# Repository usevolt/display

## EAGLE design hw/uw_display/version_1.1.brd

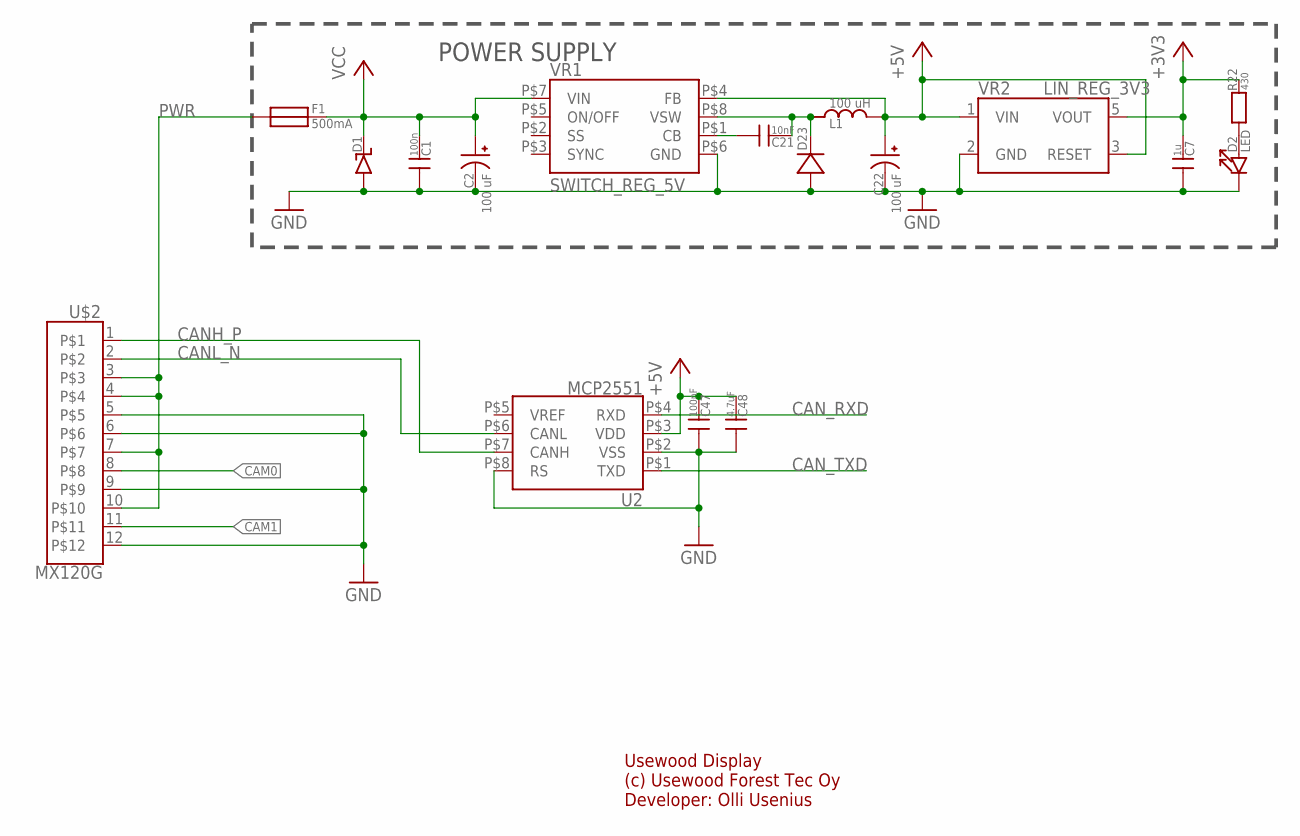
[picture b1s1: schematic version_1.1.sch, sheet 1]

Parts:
C1: 100n; 0603_SILKSCREEN
C2, C22: 100 uF; CAP_POL_SMD_10X10X10MM
C7: 1u; 0603_SILKSCREEN
C21: 10nF; 0603_SILKSCREEN
C47: 100nF; 0603_SILKSCREEN
C48: 4.7uF; 0603_SILKSCREEN
D1: DIODE_TVSDO-214AA; DO-214AB
D2: LED; 0603_SILKSCREEN
D23: DIODEDO219AB; DO219AB
F1: 500mA; MULTICOMP_MC36211
L1: 100 uH; INDUCTOR_BOURNS_10X13X5MM
R22: 430; 0603_SILKSCREEN
U2: MCP2551; SOIC8
U$2: MX120G; MOLEX_MX120G
VR1: SWITCH_REG_5V; SOIC8
VR2: LIN_REG_3V3; SOP5

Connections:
+3V3: C7.1, R22.1, VR2.5 (VOUT); also elsewhere on the board
+5V: C22.+, C47.1, C48.1, L1.P$2, U2.P$3 (VDD), VR1.P$4 (FB), VR2.1 (VIN), VR2.3 (RESET); also elsewhere on the board
CAM0: U$2.8; also elsewhere on the board
CAM1: U$2.11; also elsewhere on the board
CANH_P: U2.P$7 (CANH), U$2.1
CANL_N: U2.P$6 (CANL), U$2.2
CAN_RXD: U2.P$4 (RXD); also elsewhere on the board
CAN_TXD: U2.P$1 (TXD); also elsewhere on the board
GND: C1.0, C2.-, C7.0, C22.-, C47.0, C48.0, D1.P$1, D2.1, D23.P$1, U2.P$2 (VSS), U2.P$8 (RS), U$2.5, U$2.6, U$2.9, U$2.12, VR1.P$6 (GND), VR2.2 (GND); also elsewhere on the board
unnamed: D2.0, R22.0
unnamed: C21.1, D23.P$2 (N), L1.P$1, VR1.P$8 (VSW)
unnamed: C21.0, VR1.P$1 (CB)
PWR: F1.P$1, U$2.3, U$2.4, U$2.7, U$2.10
VCC: C1.1, C2.+, D1.P$2 (N), F1.P$2, VR1.P$7 (VIN); also elsewhere on the board

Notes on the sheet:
POWER SUPPLY
Usewood Display (c) Usewood Forest Tec Oy Developer: Olli Usenius

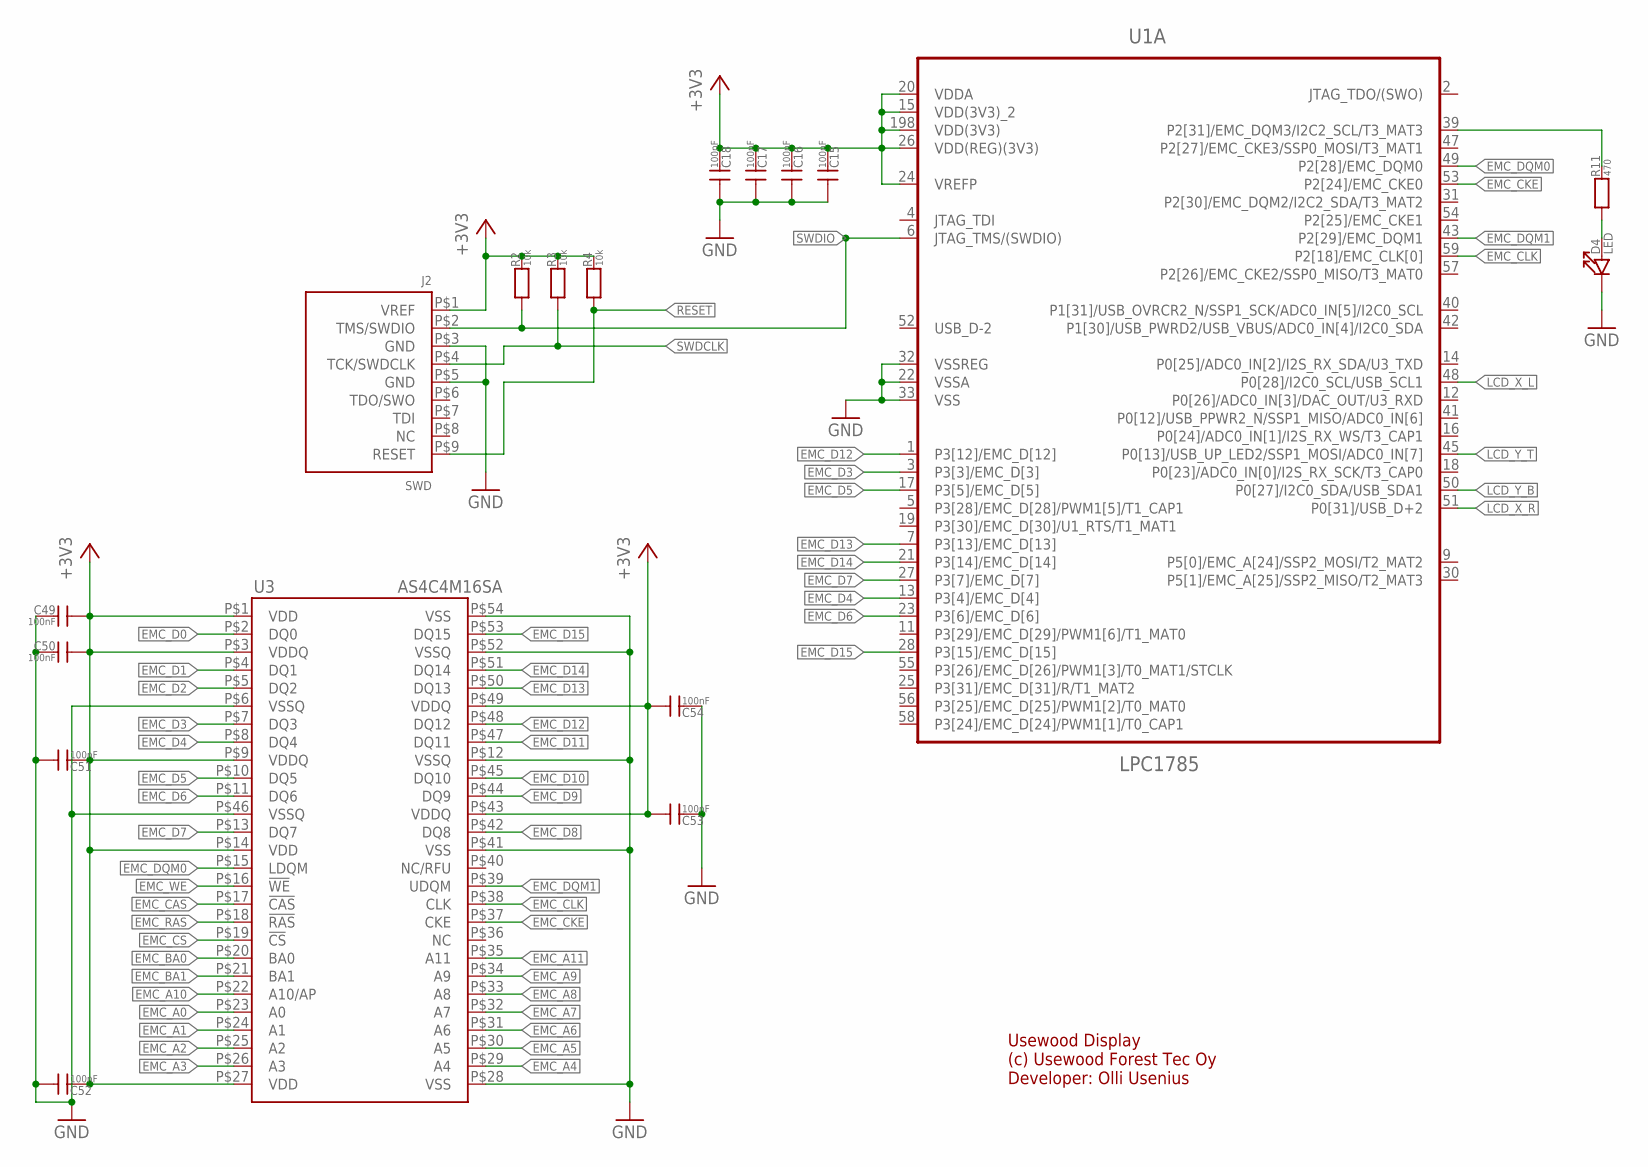
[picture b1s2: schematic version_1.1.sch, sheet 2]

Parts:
C15, C16, C17, C18, C49, C50, C51, C52, C53, C54: 100nF; 0603_SILKSCREEN
D4: LED; 0603_SILKSCREEN
J2: SWD; ARM_10_PIN_JTAG/SWD_CONNECTOR
R2, R3, R4: 10k; 0603_SILKSCREEN
R11: 470; 0603_SILKSCREEN
U1: LPC1785; QFP50P3000X3000X160-208N
U3: AS4C4M16SA; TSOP_II_54_PIN

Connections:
+3V3: C15.1, C16.1, C17.1, C18.1, C49.0, C50.0, C51.1, C52.1, C53.0, C54.0, J2.P$1 (VREF), R2.1, R3.1, R4.1, U1.15 (VDD(3V3)_2), U1.20 (VDDA), U1.24 (VREFP), U1.26 (VDD(REG)(3V3)), U1.198 (VDD(3V3)), U3.P$1 (VDD), U3.P$3 (VDDQ), U3.P$9 (VDDQ), U3.P$14 (VDD), U3.P$27 (VDD), U3.P$43 (VDDQ), U3.P$49 (VDDQ); also elsewhere on the board
EMC_A0: U3.P$23 (A0); also elsewhere on the board
EMC_A1: U3.P$24 (A1); also elsewhere on the board
EMC_A2: U3.P$25 (A2); also elsewhere on the board
EMC_A3: U3.P$26 (A3); also elsewhere on the board
EMC_A4: U3.P$29 (A4); also elsewhere on the board
EMC_A5: U3.P$30 (A5); also elsewhere on the board
EMC_A6: U3.P$31 (A6); also elsewhere on the board
EMC_A7: U3.P$32 (A7); also elsewhere on the board
EMC_A8: U3.P$33 (A8); also elsewhere on the board
EMC_A9: U3.P$34 (A9); also elsewhere on the board
EMC_A10: U3.P$22 (A10/AP); also elsewhere on the board
EMC_A11: U3.P$35 (A11); also elsewhere on the board
EMC_BA0: U3.P$20 (BA0); also elsewhere on the board
EMC_BA1: U3.P$21 (BA1); also elsewhere on the board
EMC_CAS: U3.P$17 (!CAS); also elsewhere on the board
EMC_CKE: U1.53 (P2[24]/EMC_CKE0), U3.P$37 (CKE)
EMC_CLK: U1.59 (P2[18]/EMC_CLK[0]), U3.P$38 (CLK)
EMC_CS: U3.P$19 (!CS); also elsewhere on the board
EMC_D0: U3.P$2 (DQ0); also elsewhere on the board
EMC_D1: U3.P$4 (DQ1); also elsewhere on the board
EMC_D2: U3.P$5 (DQ2); also elsewhere on the board
EMC_D3: U1.3 (P3[3]/EMC_D[3]), U3.P$7 (DQ3)
EMC_D4: U1.13 (P3[4]/EMC_D[4]), U3.P$8 (DQ4)
EMC_D5: U1.17 (P3[5]/EMC_D[5]), U3.P$10 (DQ5)
EMC_D6: U1.23 (P3[6]/EMC_D[6]), U3.P$11 (DQ6)
EMC_D7: U1.27 (P3[7]/EMC_D[7]), U3.P$13 (DQ7)
EMC_D8: U3.P$42 (DQ8); also elsewhere on the board
EMC_D9: U3.P$44 (DQ9); also elsewhere on the board
EMC_D10: U3.P$45 (DQ10); also elsewhere on the board
EMC_D11: U3.P$47 (DQ11); also elsewhere on the board
EMC_D12: U1.1 (P3[12]/EMC_D[12]), U3.P$48 (DQ12)
EMC_D13: U1.7 (P3[13]/EMC_D[13]), U3.P$50 (DQ13)
EMC_D14: U1.21 (P3[14]/EMC_D[14]), U3.P$51 (DQ14)
EMC_D15: U1.28 (P3[15]/EMC_D[15]), U3.P$53 (DQ15)
EMC_DQM0: U1.49 (P2[28]/EMC_DQM0), U3.P$15 (LDQM)
EMC_DQM1: U1.43 (P2[29]/EMC_DQM1), U3.P$39 (UDQM)
EMC_RAS: U3.P$18 (!RAS); also elsewhere on the board
EMC_WE: U3.P$16 (!WE); also elsewhere on the board
GND: C15.0, C16.0, C17.0, C18.0, C49.1, C50.1, C51.0, C52.0, C53.1, C54.1, D4.1, J2.P$3 (GND), J2.P$5 (GND), U1.22 (VSSA), U1.32 (VSSREG), U1.33 (VSS), U3.P$6 (VSSQ), U3.P$12 (VSSQ), U3.P$28 (VSS), U3.P$41 (VSS), U3.P$46 (VSSQ), U3.P$52 (VSSQ), U3.P$54 (VSS); also elsewhere on the board
LCD_X_L: U1.48 (P0[28]/I2C0_SCL/USB_SCL1); also elsewhere on the board
LCD_X_R: U1.51 (P0[31]/USB_D+2); also elsewhere on the board
LCD_Y_B: U1.50 (P0[27]/I2C0_SDA/USB_SDA1); also elsewhere on the board
LCD_Y_T: U1.45 (P0[13]/USB_UP_LED2/SSP1_MOSI/ADC0_IN[7]); also elsewhere on the board
unnamed: D4.0, R11.0
unnamed: R11.1, U1.39 (P2[31]/EMC_DQM3/I2C2_SCL/T3_MAT3)
RESET: J2.P$9 (RESET), R4.0; also elsewhere on the board
SWDCLK: J2.P$4 (TCK/SWDCLK), R3.0; also elsewhere on the board
SWDIO: J2.P$2 (TMS/SWDIO), R2.0, U1.6 (JTAG_TMS/(SWDIO))

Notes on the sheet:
Usewood Display (c) Usewood Forest Tec Oy Developer: Olli Usenius

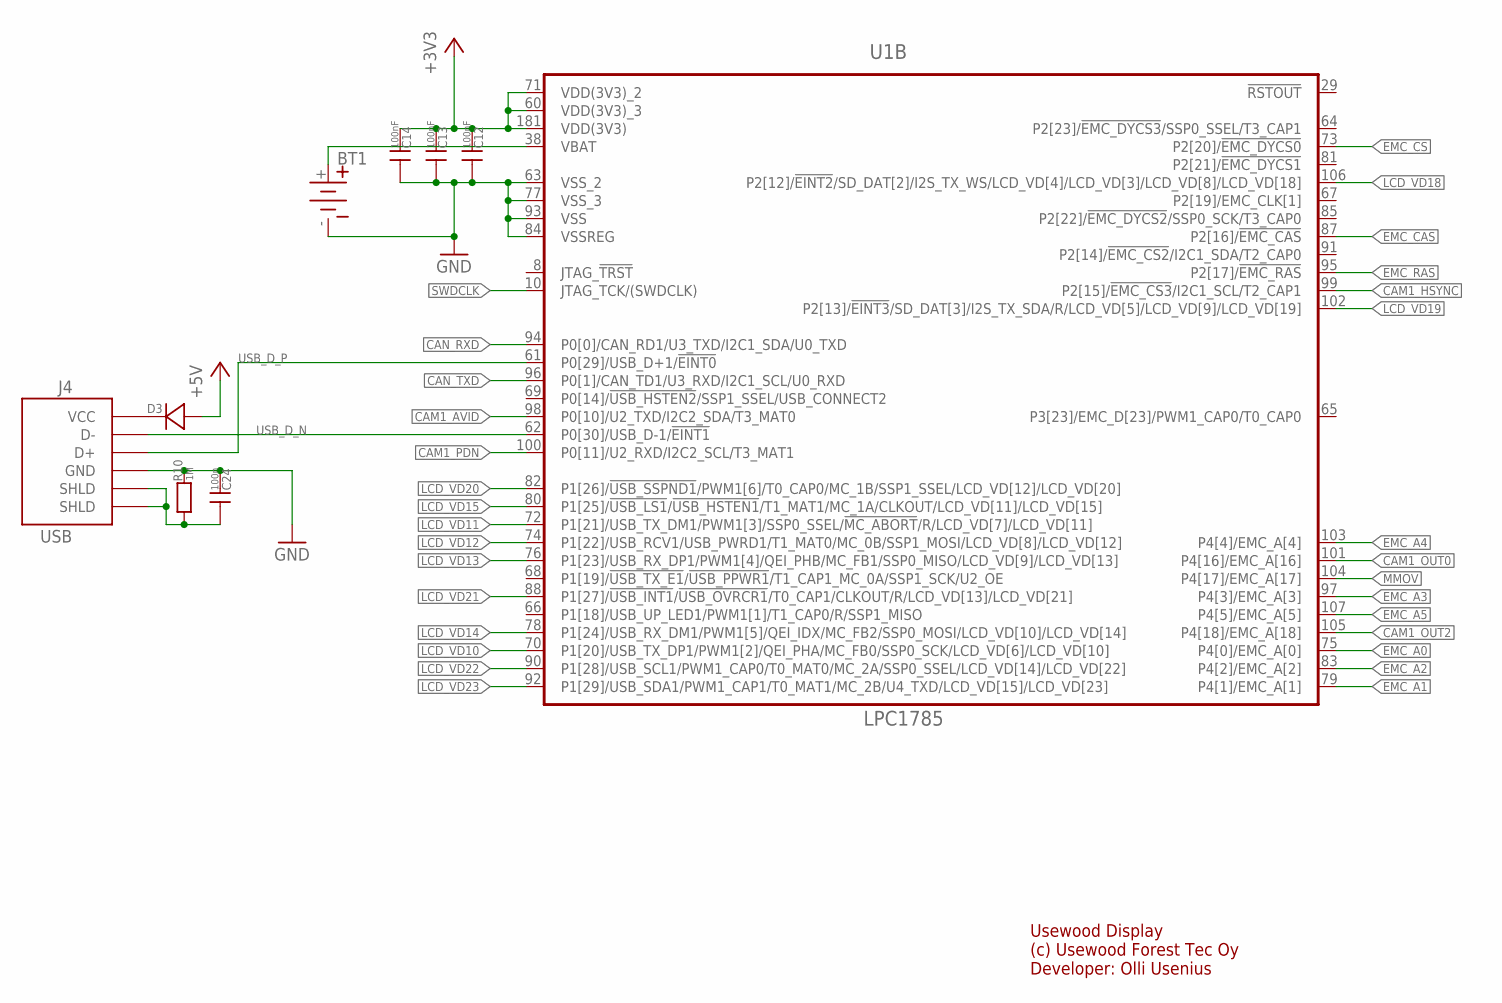
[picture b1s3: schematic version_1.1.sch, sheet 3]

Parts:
BT1: BAT; BATTERY_HOLDER_COIN_20MM_SMD
C12, C13, C14: 100nF; 0603_SILKSCREEN
C24: 100n; 0603_SILKSCREEN
D3: DIODEDO219AB; DO219AB
J4: USB; USB_A_RECEPTACLE_VERTICAL_MULTICOMP
R10: 1M; 0603_SILKSCREEN
U1: LPC1785; QFP50P3000X3000X160-208N

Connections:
+3V3: C12.1, C13.1, C14.1, U1.60 (VDD(3V3)_3), U1.71 (VDD(3V3)_2), U1.181 (VDD(3V3)); also elsewhere on the board
+5V: D3.P$1; also elsewhere on the board
CAM1_AVID: U1.98 (P0[10]/U2_TXD/I2C2_SDA/T3_MAT0); also elsewhere on the board
CAM1_HSYNC: U1.99 (P2[15]/!EMC_CS3!/I2C1_SCL/T2_CAP1); also elsewhere on the board
CAM1_OUT0: U1.101 (P4[16]/EMC_A[16]); also elsewhere on the board
CAM1_OUT2: U1.105 (P4[18]/EMC_A[18]); also elsewhere on the board
CAM1_PDN: U1.100 (P0[11]/U2_RXD/I2C2_SCL/T3_MAT1); also elsewhere on the board
CAN_RXD: U1.94 (P0[0]/CAN_RD1/U3_TXD/I2C1_SDA/U0_TXD); also elsewhere on the board
CAN_TXD: U1.96 (P0[1]/CAN_TD1/U3_RXD/I2C1_SCL/U0_RXD); also elsewhere on the board
EMC_A0: U1.75 (P4[0]/EMC_A[0]); also elsewhere on the board
EMC_A1: U1.79 (P4[1]/EMC_A[1]); also elsewhere on the board
EMC_A2: U1.83 (P4[2]/EMC_A[2]); also elsewhere on the board
EMC_A3: U1.97 (P4[3]/EMC_A[3]); also elsewhere on the board
EMC_A4: U1.103 (P4[4]/EMC_A[4]); also elsewhere on the board
EMC_A5: U1.107 (P4[5]/EMC_A[5]); also elsewhere on the board
EMC_CAS: U1.87 (P2[16]/!EMC_CAS!); also elsewhere on the board
EMC_CS: U1.73 (P2[20]/!EMC_DYCS0); also elsewhere on the board
EMC_RAS: U1.95 (P2[17]/!EMC_RAS); also elsewhere on the board
GND: BT1.-, C12.0, C13.0, C14.0, C24.1, J4.P$4 (GND), R10.1, U1.63 (VSS_2), U1.77 (VSS_3), U1.84 (VSSREG), U1.93 (VSS); also elsewhere on the board
LCD_VD10: U1.70 (P1[20]/USB_TX_DP1/PWM1[2]/QEI_PHA/MC_FB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); also elsewhere on the board
LCD_VD11: U1.72 (P1[21]/USB_TX_DM1/PWM1[3]/SSP0_SSEL/!MC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); also elsewhere on the board
LCD_VD12: U1.74 (P1[22]/USB_RCV1/USB_PWRD1/T1_MAT0/MC_0B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); also elsewhere on the board
LCD_VD13: U1.76 (P1[23]/USB_RX_DP1/PWM1[4]/QEI_PHB/MC_FB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); also elsewhere on the board
LCD_VD14: U1.78 (P1[24]/USB_RX_DM1/PWM1[5]/QEI_IDX/MC_FB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); also elsewhere on the board
LCD_VD15: U1.80 (P1[25]/!USB_LS1!/!USB_HSTEN1!/T1_MAT1/M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); also elsewhere on the board
LCD_VD18: U1.106 (P2[12]/!EINT2!/SD_DAT[2]/I2S_TX_WS/LCD_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); also elsewhere on the board
LCD_VD19: U1.102 (P2[13]/!EINT3!/SD_DAT[3]/I2S_TX_SDA/R/L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); also elsewhere on the board
LCD_VD20: U1.82 (P1[26]/!USB_SSPND1!/PWM1[6]/T0_CAP0/MC_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); also elsewhere on the board
LCD_VD21: U1.88 (P1[27]/!USB_INT1!/!USB_OVRCR1!/T0_CAP1/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); also elsewhere on the board
LCD_VD22: U1.90 (P1[28]/USB_SCL1/PWM1_CAP0/T0_MAT0/MC_2A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); also elsewhere on the board
LCD_VD23: U1.92 (P1[29]/USB_SDA1/PWM1_CAP1/T0_MAT1/MC_2B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); also elsewhere on the board
MMOV: U1.104 (P4[17]/EMC_A[17]); also elsewhere on the board
unnamed: BT1.+, U1.38 (VBAT)
unnamed: D3.P$2 (N), J4.P$1 (VCC)
unnamed: C24.0, J4.P$5 (SHLD), J4.P$6 (SHLD), R10.0
SWDCLK: U1.10 (JTAG_TCK/(SWDCLK)); also elsewhere on the board
USB_D_N: J4.P$2 (D-), U1.62 (P0[30]/USB_D-1/!EINT1)
USB_D_P: J4.P$3 (D+), U1.61 (P0[29]/USB_D+1/!EINT0)

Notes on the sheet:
Usewood Display (c) Usewood Forest Tec Oy Developer: Olli Usenius

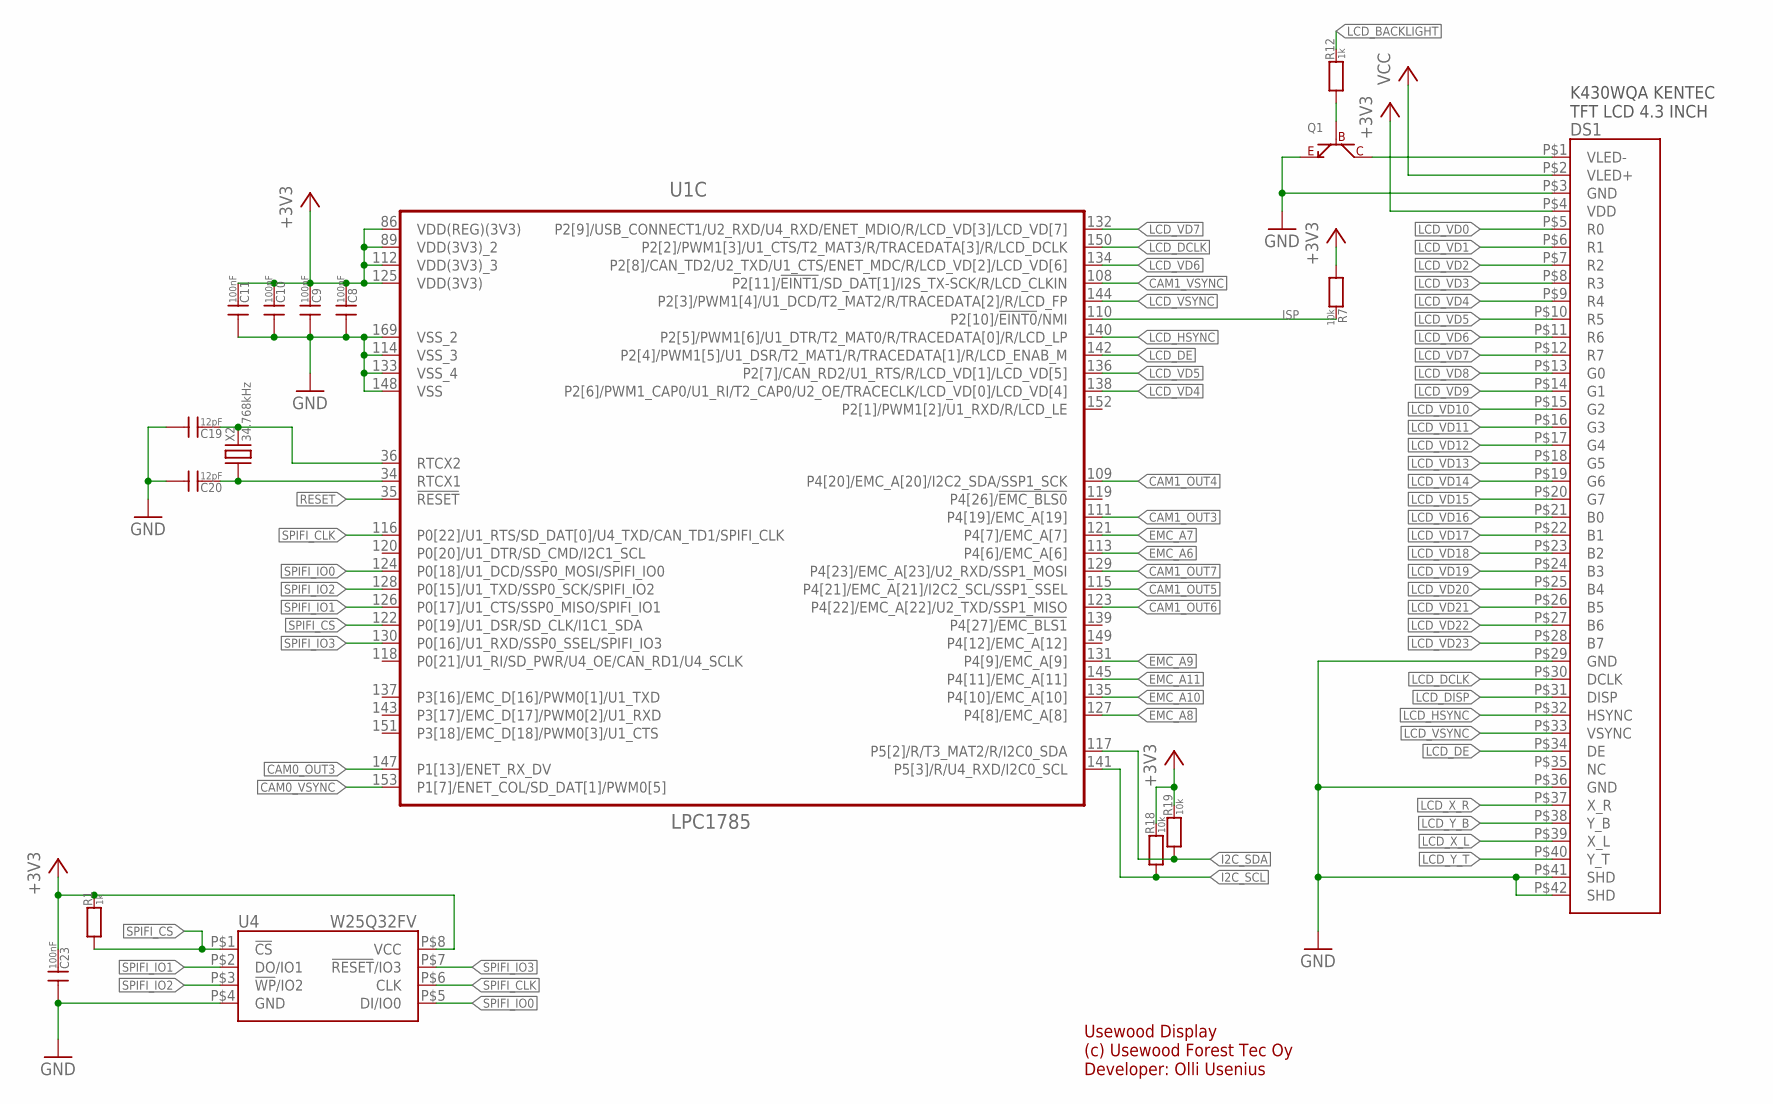
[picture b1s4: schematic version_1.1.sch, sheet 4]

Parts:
C8, C9, C10, C11, C23: 100nF; 0603_SILKSCREEN
C19, C20: 12pF; 0603_SILKSCREEN
DS1: KENTEC_TFT_LCD_4.3_INCHSMD; HEADER_KENTEC_TFT_LCD_4.3_INCH
Q1: NPN_TRANSISTORSOT323; SOT323
R1, R12: 1k; 0603_SILKSCREEN
R7, R18, R19: 10k; 0603_SILKSCREEN
U1: LPC1785; QFP50P3000X3000X160-208N
U4: W25Q32FV; SOIC8_W
X2: 34.768kHz; XTAL_ABS25

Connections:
+3V3: C8.1, C9.1, C10.1, C11.1, C23.1, DS1.P$4 (VDD), R1.1, R7.0, R18.1, R19.1, U1.86 (VDD(REG)(3V3)), U1.89 (VDD(3V3)_2), U1.112 (VDD(3V3)_3), U1.125 (VDD(3V3)), U4.P$8 (VCC); also elsewhere on the board
CAM0_OUT3: U1.147 (P1[13]/ENET_RX_DV); also elsewhere on the board
CAM0_VSYNC: U1.153 (P1[7]/ENET_COL/SD_DAT[1]/PWM0[5]); also elsewhere on the board
CAM1_OUT3: U1.111 (P4[19]/EMC_A[19]); also elsewhere on the board
CAM1_OUT4: U1.109 (P4[20]/EMC_A[20]/I2C2_SDA/SSP1_SCK); also elsewhere on the board
CAM1_OUT5: U1.115 (P4[21]/EMC_A[21]/I2C2_SCL/SSP1_SSEL); also elsewhere on the board
CAM1_OUT6: U1.123 (P4[22]/EMC_A[22]/U2_TXD/SSP1_MISO); also elsewhere on the board
CAM1_OUT7: U1.129 (P4[23]/EMC_A[23]/U2_RXD/SSP1_MOSI); also elsewhere on the board
CAM1_VSYNC: U1.108 (P2[11]/!EINT1!/SD_DAT[1]/I2S_TX-SCK/R/L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); also elsewhere on the board
EMC_A6: U1.113 (P4[6]/EMC_A[6]); also elsewhere on the board
EMC_A7: U1.121 (P4[7]/EMC_A[7]); also elsewhere on the board
EMC_A8: U1.127 (P4[8]/EMC_A[8]); also elsewhere on the board
EMC_A9: U1.131 (P4[9]/EMC_A[9]); also elsewhere on the board
EMC_A10: U1.135 (P4[10]/EMC_A[10]); also elsewhere on the board
EMC_A11: U1.145 (P4[11]/EMC_A[11]); also elsewhere on the board
GND: C8.0, C9.0, C10.0, C11.0, C19.0, C20.0, C23.0, DS1.P$3 (GND), DS1.P$29 (GND), DS1.P$36 (GND), DS1.P$41 (SHD), DS1.P$42 (SHD), Q1.R (E), U1.114 (VSS_3), U1.133 (VSS_4), U1.148 (VSS), U1.169 (VSS_2), U4.P$4 (GND); also elsewhere on the board
I2C_SCL: R18.0, U1.141 (P5[3]/R/U4_RXD/I2C0_SCL); also elsewhere on the board
I2C_SDA: R19.0, U1.117 (P5[2]/R/T3_MAT2/R/I2C0_SDA); also elsewhere on the board
ISP: R7.1, U1.110 (P2[10]/!EINT0!/NMI)
LCD_BACKLIGHT: R12.1; also elsewhere on the board
LCD_DCLK: DS1.P$30 (DCLK), U1.150 (P2[2]/PWM1[3]/U1_CTS/T2_MAT3/R/TRACEDAT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)
LCD_DE: DS1.P$34 (DE), U1.142 (P2[4]/PWM1[5]/U1_DSR/T2_MAT1/R/TRACEDAT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)
LCD_DISP: DS1.P$31 (DISP); also elsewhere on the board
LCD_HSYNC: DS1.P$32 (HSYNC), U1.140 (P2[5]/PWM1[6]/U1_DTR/T2_MAT0/R/TRACEDAT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)
LCD_VD0: DS1.P$5 (R0); also elsewhere on the board
LCD_VD1: DS1.P$6 (R1); also elsewhere on the board
LCD_VD2: DS1.P$7 (R2); also elsewhere on the board
LCD_VD3: DS1.P$8 (R3); also elsewhere on the board
LCD_VD4: DS1.P$9 (R4), U1.138 (P2[6]/PWM1_CAP0/U1_RI/T2_CAP0/U2_OE/TRA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)
LCD_VD5: DS1.P$10 (R5), U1.136 (P2[7]/CAN_RD2/U1_RTS/R/LCD_VD[1]/LCD_VD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)
LCD_VD6: DS1.P$11 (R6), U1.134 (P2[8]/CAN_TD2/U2_TXD/U1_CTS/ENET_MDC/R/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)
LCD_VD7: DS1.P$12 (R7), U1.132 (P2[9]/USB_CONNECT1/U2_RXD/U4_RXD/ENET_M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)
LCD_VD8: DS1.P$13 (G0); also elsewhere on the board
LCD_VD9: DS1.P$14 (G1); also elsewhere on the board
LCD_VD10: DS1.P$15 (G2); also elsewhere on the board
LCD_VD11: DS1.P$16 (G3); also elsewhere on the board
LCD_VD12: DS1.P$17 (G4); also elsewhere on the board
LCD_VD13: DS1.P$18 (G5); also elsewhere on the board
LCD_VD14: DS1.P$19 (G6); also elsewhere on the board
LCD_VD15: DS1.P$20 (G7); also elsewhere on the board
LCD_VD16: DS1.P$21 (B0); also elsewhere on the board
LCD_VD17: DS1.P$22 (B1); also elsewhere on the board
LCD_VD18: DS1.P$23 (B2); also elsewhere on the board
LCD_VD19: DS1.P$24 (B3); also elsewhere on the board
LCD_VD20: DS1.P$25 (B4); also elsewhere on the board
LCD_VD21: DS1.P$26 (B5); also elsewhere on the board
LCD_VD22: DS1.P$27 (B6); also elsewhere on the board
LCD_VD23: DS1.P$28 (B7); also elsewhere on the board
LCD_VLED-: DS1.P$1 (VLED-), Q1.M (C)
LCD_VSYNC: DS1.P$33 (VSYNC), U1.144 (P2[3]/PWM1[4]/U1_DCD/T2_MAT2/R/TRACEDAT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)
LCD_X_L: DS1.P$39 (X_L); also elsewhere on the board
LCD_X_R: DS1.P$37 (X_R); also elsewhere on the board
LCD_Y_B: DS1.P$38 (Y_B); also elsewhere on the board
LCD_Y_T: DS1.P$40 (Y_T); also elsewhere on the board
unnamed: Q1.L (B), R12.0
unnamed: C20.1, U1.34 (RTCX1), X2.1
unnamed: C19.1, U1.36 (RTCX2), X2.4
RESET: U1.35 (!RESET); also elsewhere on the board
SPIFI_CLK: U1.116 (P0[22]/U1_RTS/SD_DAT[0]/U4_TXD/CAN_TD1/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), U4.P$6 (CLK)
SPIFI_CS: R1.0, U1.122 (P0[19]/U1_DSR/SD_CLK/I1C1_SDA), U4.P$1 (!CS)
SPIFI_IO0: U1.124 (P0[18]/U1_DCD/SSP0_MOSI/SPIFI_IO0), U4.P$5 (DI/IO0)
SPIFI_IO1: U1.126 (P0[17]/U1_CTS/SSP0_MISO/SPIFI_IO1), U4.P$2 (DO/IO1)
SPIFI_IO2: U1.128 (P0[15]/U1_TXD/SSP0_SCK/SPIFI_IO2), U4.P$3 (!WP!/IO2)
SPIFI_IO3: U1.130 (P0[16]/U1_RXD/SSP0_SSEL/SPIFI_IO3), U4.P$7 (!RESET!/IO3)
VCC: DS1.P$2 (VLED+); also elsewhere on the board

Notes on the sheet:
Usewood Display (c) Usewood Forest Tec Oy Developer: Olli Usenius

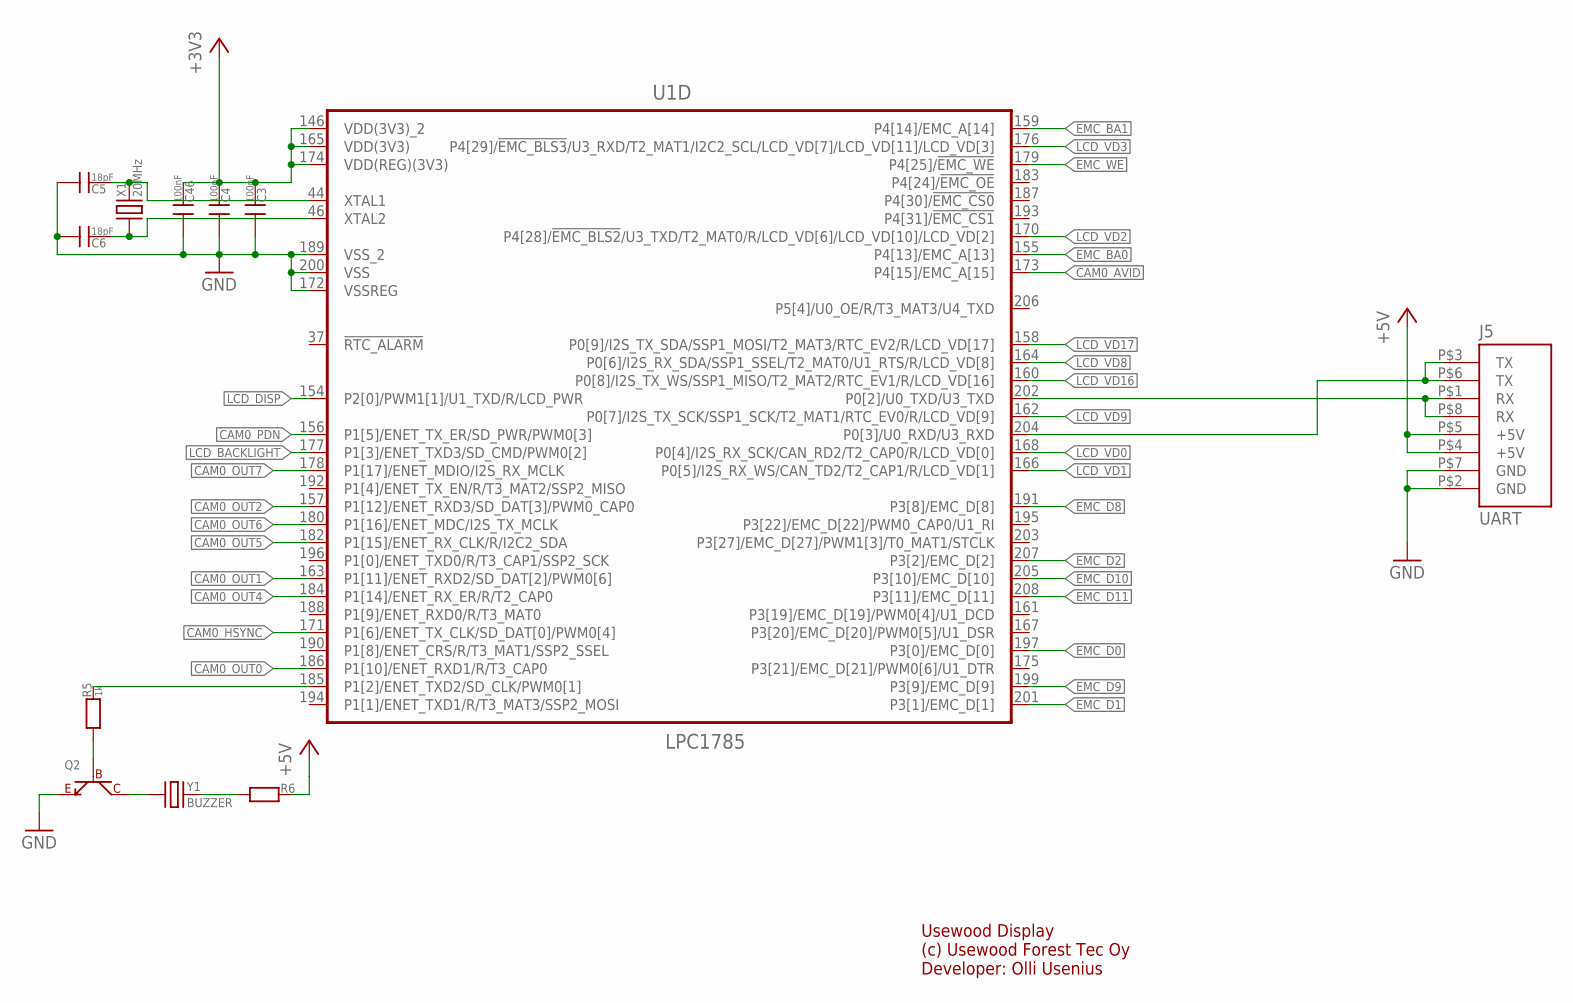
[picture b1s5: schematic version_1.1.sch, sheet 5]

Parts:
C3, C4, C46: 100nF; 0603_SILKSCREEN
C5, C6: 18pF; 0603_SILKSCREEN
J5: UART; HEADER_4_2_SMD
Q2: NPN_TRANSISTORSOT323; SOT323
R5: 1k; 0603_SILKSCREEN
R6: RES_0603; 0603_SILKSCREEN
U1: LPC1785; QFP50P3000X3000X160-208N
X1: 20MHz; XTAL_SMD_5X3.2
Y1: BUZZER; PIEZO_SOUNDER_MURATA

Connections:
+3V3: C3.1, C4.1, C46.1, U1.146 (VDD(3V3)_2), U1.165 (VDD(3V3)), U1.174 (VDD(REG)(3V3)); also elsewhere on the board
+5V: J5.P$4 (+5V), J5.P$5 (+5V), R6.1; also elsewhere on the board
CAM0_AVID: U1.173 (P4[15]/EMC_A[15]); also elsewhere on the board
CAM0_HSYNC: U1.171 (P1[6]/ENET_TX_CLK/SD_DAT[0]/PWM0[4]); also elsewhere on the board
CAM0_OUT0: U1.186 (P1[10]/ENET_RXD1/R/T3_CAP0); also elsewhere on the board
CAM0_OUT1: U1.163 (P1[11]/ENET_RXD2/SD_DAT[2]/PWM0[6]); also elsewhere on the board
CAM0_OUT2: U1.157 (P1[12]/ENET_RXD3/SD_DAT[3]/PWM0_CAP0); also elsewhere on the board
CAM0_OUT4: U1.184 (P1[14]/ENET_RX_ER/R/T2_CAP0); also elsewhere on the board
CAM0_OUT5: U1.182 (P1[15]/ENET_RX_CLK/R/I2C2_SDA); also elsewhere on the board
CAM0_OUT6: U1.180 (P1[16]/ENET_MDC/I2S_TX_MCLK); also elsewhere on the board
CAM0_OUT7: U1.178 (P1[17]/ENET_MDIO/I2S_RX_MCLK); also elsewhere on the board
CAM0_PDN: U1.156 (P1[5]/ENET_TX_ER/SD_PWR/PWM0[3]); also elsewhere on the board
EMC_BA0: U1.155 (P4[13]/EMC_A[13]); also elsewhere on the board
EMC_BA1: U1.159 (P4[14]/EMC_A[14]); also elsewhere on the board
EMC_D0: U1.197 (P3[0]/EMC_D[0]); also elsewhere on the board
EMC_D1: U1.201 (P3[1]/EMC_D[1]); also elsewhere on the board
EMC_D2: U1.207 (P3[2]/EMC_D[2]); also elsewhere on the board
EMC_D8: U1.191 (P3[8]/EMC_D[8]); also elsewhere on the board
EMC_D9: U1.199 (P3[9]/EMC_D[9]); also elsewhere on the board
EMC_D10: U1.205 (P3[10]/EMC_D[10]); also elsewhere on the board
EMC_D11: U1.208 (P3[11]/EMC_D[11]); also elsewhere on the board
EMC_WE: U1.179 (P4[25]/!EMC_WE); also elsewhere on the board
GND: C3.0, C4.0, C5.0, C6.0, C46.0, J5.P$2 (GND), J5.P$7 (GND), Q2.R (E), U1.172 (VSSREG), U1.189 (VSS_2), U1.200 (VSS); also elsewhere on the board
LCD_BACKLIGHT: U1.177 (P1[3]/ENET_TXD3/SD_CMD/PWM0[2]); also elsewhere on the board
LCD_DISP: U1.154 (P2[0]/PWM1[1]/U1_TXD/R/LCD_PWR); also elsewhere on the board
LCD_VD0: U1.168 (P0[4]/I2S_RX_SCK/CAN_RD2/T2_CAP0/R/LCD_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); also elsewhere on the board
LCD_VD1: U1.166 (P0[5]/I2S_RX_WS/CAN_TD2/T2_CAP1/R/LCD_V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); also elsewhere on the board
LCD_VD2: U1.170 (P4[28]/!EMC_BLS2!/U3_TXD/T2_MAT0/R/LCD_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); also elsewhere on the board
LCD_VD3: U1.176 (P4[29]/!EMC_BLS3!/U3_RXD/T2_MAT1/I2C2_S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); also elsewhere on the board
LCD_VD8: U1.164 (P0[6]/I2S_RX_SDA/SSP1_SSEL/T2_MAT0/U1_R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); also elsewhere on the board
LCD_VD9: U1.162 (P0[7]/I2S_TX_SCK/SSP1_SCK/T2_MAT1/RTC_E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); also elsewhere on the board
LCD_VD16: U1.160 (P0[8]/I2S_TX_WS/SSP1_MISO/T2_MAT2/RTC_E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); also elsewhere on the board
LCD_VD17: U1.158 (P0[9]/I2S_TX_SDA/SSP1_MOSI/T2_MAT3/RTC_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); also elsewhere on the board
unnamed: Q2.L (B), R5.0
unnamed: C5.1, U1.44 (XTAL1), X1.P$2
unnamed: C6.1, U1.46 (XTAL2), X1.P$1
unnamed: Q2.M (C), Y1.P$1
unnamed: J5.P$1 (RX), J5.P$8 (RX), U1.202 (P0[2]/U0_TXD/U3_TXD)
unnamed: J5.P$3 (TX), J5.P$6 (TX), U1.204 (P0[3]/U0_RXD/U3_RXD)
unnamed: R5.1, U1.185 (P1[2]/ENET_TXD2/SD_CLK/PWM0[1])
unnamed: R6.0, Y1.P$2

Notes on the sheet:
Usewood Display (c) Usewood Forest Tec Oy Developer: Olli Usenius

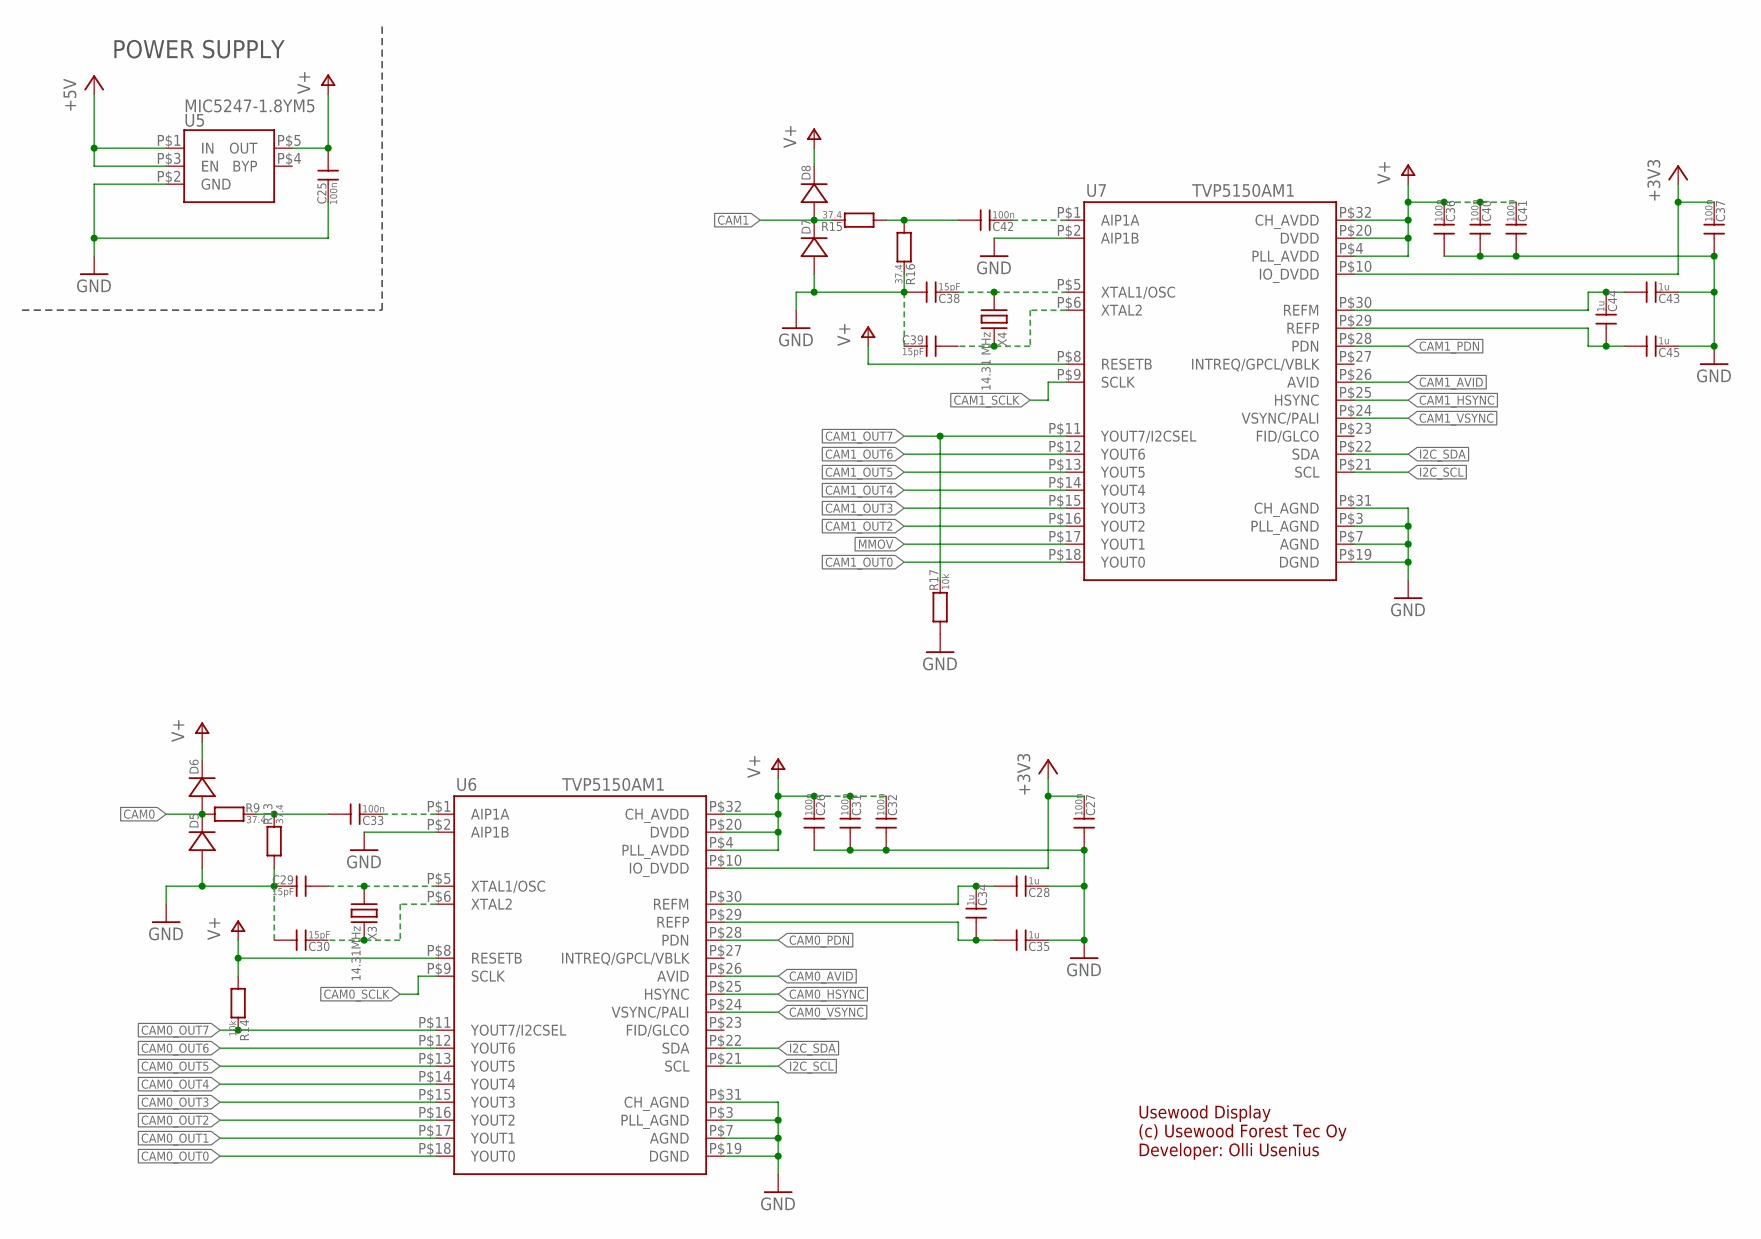
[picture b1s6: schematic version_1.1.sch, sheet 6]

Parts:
C25, C26, C27, C31, C32, C33, C36, C37, C40, C41, C42: 100n; 0603_SILKSCREEN
C28, C34, C35, C43, C44, C45: 1u; 0603_SILKSCREEN
C29, C30, C38, C39: 15pF; 0603_SILKSCREEN
D5, D6, D7, D8: DIODEDO219AB; DO219AB
R9, R13, R15, R16: 37.4; 0603_SILKSCREEN
R14, R17: 10k; 0603_SILKSCREEN
U5: MIC5247-1.8YM5; SOT-23
U6, U7: TVP5150AM1; QFP32
X3: 14.31MHz; XTAL_SMD_3.2X2.5
X4: 14.31 MHz; XTAL_SMD_3.2X2.5

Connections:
+3V3: C27.1, C37.1, U6.P$10 (IO_DVDD), U7.P$10 (IO_DVDD); also elsewhere on the board
+5V: U5.P$1 (IN), U5.P$3 (EN); also elsewhere on the board
CAM0: D5.P$2 (N), D6.P$1, R9.0; also elsewhere on the board
CAM0_AVID: U6.P$26 (AVID); also elsewhere on the board
CAM0_HSYNC: U6.P$25 (HSYNC); also elsewhere on the board
CAM0_OUT0: U6.P$18 (YOUT0); also elsewhere on the board
CAM0_OUT1: U6.P$17 (YOUT1); also elsewhere on the board
CAM0_OUT2: U6.P$16 (YOUT2); also elsewhere on the board
CAM0_OUT3: U6.P$15 (YOUT3); also elsewhere on the board
CAM0_OUT4: U6.P$14 (YOUT4); also elsewhere on the board
CAM0_OUT5: U6.P$13 (YOUT5); also elsewhere on the board
CAM0_OUT6: U6.P$12 (YOUT6); also elsewhere on the board
CAM0_OUT7: R14.1, U6.P$11 (YOUT7/I2CSEL); also elsewhere on the board
CAM0_PDN: U6.P$28 (PDN); also elsewhere on the board
CAM0_SCLK: U6.P$9 (SCLK)
CAM0_VSYNC: U6.P$24 (VSYNC/PALI); also elsewhere on the board
CAM1: D7.P$2 (N), D8.P$1, R15.1; also elsewhere on the board
CAM1_AVID: U7.P$26 (AVID); also elsewhere on the board
CAM1_HSYNC: U7.P$25 (HSYNC); also elsewhere on the board
CAM1_OUT0: U7.P$18 (YOUT0); also elsewhere on the board
CAM1_OUT2: U7.P$16 (YOUT2); also elsewhere on the board
CAM1_OUT3: U7.P$15 (YOUT3); also elsewhere on the board
CAM1_OUT4: U7.P$14 (YOUT4); also elsewhere on the board
CAM1_OUT5: U7.P$13 (YOUT5); also elsewhere on the board
CAM1_OUT6: U7.P$12 (YOUT6); also elsewhere on the board
CAM1_OUT7: R17.1, U7.P$11 (YOUT7/I2CSEL); also elsewhere on the board
CAM1_PDN: U7.P$28 (PDN); also elsewhere on the board
CAM1_SCLK: U7.P$9 (SCLK)
CAM1_VSYNC: U7.P$24 (VSYNC/PALI); also elsewhere on the board
GND: C25.1, C26.0, C27.0, C28.1, C29.1, C30.0, C31.0, C32.0, C35.1, C36.0, C37.0, C38.0, C39.1, C40.0, C41.0, C43.1, C45.1, D5.P$1, D7.P$1, R13.0, R16.1, R17.0, U5.P$2 (GND), U6.P$2 (AIP1B), U6.P$3 (PLL_AGND), U6.P$7 (AGND), U6.P$19 (DGND), U6.P$31 (CH_AGND), U7.P$2 (AIP1B), U7.P$3 (PLL_AGND), U7.P$7 (AGND), U7.P$19 (DGND), U7.P$31 (CH_AGND); also elsewhere on the board
I2C_SCL: U6.P$21 (SCL), U7.P$21 (SCL); also elsewhere on the board
I2C_SDA: U6.P$22 (SDA), U7.P$22 (SDA); also elsewhere on the board
MMOV: U7.P$17 (YOUT1); also elsewhere on the board
unnamed: C29.0, U6.P$5 (XTAL1/OSC), X3.P$4
unnamed: C33.0, R9.1, R13.1
unnamed: C30.1, U6.P$6 (XTAL2), X3.P$2
unnamed: C33.1, U6.P$1 (AIP1A)
unnamed: C28.0, C34.1, U6.P$30 (REFM)
unnamed: C34.0, C35.0, U6.P$29 (REFP)
unnamed: C38.1, U7.P$5 (XTAL1/OSC), X4.P$4
unnamed: C39.0, U7.P$6 (XTAL2), X4.P$2
unnamed: C42.1, U7.P$1 (AIP1A)
unnamed: C42.0, R15.0, R16.0
unnamed: C43.0, C44.1, U7.P$30 (REFM)
unnamed: C44.0, C45.0, U7.P$29 (REFP)
V+: C25.0, C26.1, C31.1, C32.1, C36.1, C40.1, C41.1, D6.P$2 (N), D8.P$2 (N), R14.0, U5.P$5 (OUT), U6.P$4 (PLL_AVDD), U6.P$8 (RESETB), U6.P$20 (DVDD), U6.P$32 (CH_AVDD), U7.P$4 (PLL_AVDD), U7.P$8 (RESETB), U7.P$20 (DVDD), U7.P$32 (CH_AVDD)

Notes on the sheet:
Usewood Display (c) Usewood Forest Tec Oy Developer: Olli Usenius
POWER SUPPLY
